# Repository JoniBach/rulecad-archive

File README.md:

# rulecad archive

## Experiments

- **[The robot shoulder printed in place: one print, nothing to assemble but the motor](experiments/print-in-place/)** (2026-11-23): The bench shoulder's compound planetary drawn to come off the bed in one piece: every gap the printer's print gap, herringbone teeth, no carrier, checked by Manifold for gaps and by the slicer's eye for supports. Side by side with the assembled 38:1, with the play each is predicted to have. Predictions only so far: nothing has been printed. [On the site](https://jonibach.github.io/rulecad-archive/experiments/print-in-place/)
- **[What to print to test fixings and frames: five coupons, then a frame](experiments/frames-print-list/)** (2026-11-21): The coupons that turn the fixings and frames estimates into measurements: fixings and holds (pins, magnets, printed bolts), slot, joint rig and printed beam, with what each needs, what it measures and the command that writes it back. [On the site](https://jonibach.github.io/rulecad-archive/experiments/frames-print-list/)
- **[A case of printed beams: a Raspberry Pi 4 case with no bar to buy](experiments/printed-case/)** (2026-11-20): A small case of 2020 beams drawn in aluminium, every beam found printable in PETG, then drawn printed: posts and rails standing up from MISUMI's section, the cross beam lying down from the kit's printable profile, printed brackets, gussets, panels' clips, feet, the board's mount and a fan mount, all on one plate of 73 parts that prints clean. The sag under the board both ways. Predictions only so far: nothing has been printed. [On the site](https://jonibach.github.io/rulecad-archive/experiments/printed-case/)
- **[A frame of beams with a moving axis: cut, drilled, printed and built from one assembly](experiments/frames/)** (2026-11-17): A box of 2020 placed by its ends, with blind joins, printed brackets, feet and a NEMA 17 driving a carriage along its top: the cut list from one bar, a sheet per beam, eight jigs, every printed part on one plate, 37 build steps, and a trapped nut and a plate for the wrong slots caught. Predictions only so far: nothing has been cut or printed. [On the site](https://jonibach.github.io/rulecad-archive/experiments/frames/)
- **[Fixings from rules: a bracket screwed on, and the coupon that measures it](experiments/fixings/)** (2026-11-15): @rulecad/fixings in designs (v.fixings) and fasten in assemblies: each screw followed along its axis for its holes, its far end, its length, its thread, its seat, its key and its load. A shelf bracket with a pilot, an insert boss and nuts in slots, and the fixings coupon to print; measurements to come. [On the site](https://jonibach.github.io/rulecad-archive/experiments/fixings/)
- **[An arm that draws, then lifts, then a leg: checked before it's printed](experiments/robots/)** (2026-11-10): A SCARA arm sized from its task, the same parts upright with a gripper and a Z axis, and a leg from the arm's gearbox, with reach, speed, an error budget, bearing and link loads, wiring, a shopping list and a build page from one assembly. Predictions only so far: nothing has been printed or moved. [On the site](https://jonibach.github.io/rulecad-archive/experiments/robots/)
- **[What to print to test the robots: benchmarks, then the arm, then the leg](experiments/robots-print-list/)** (2026-11-10): The print list and measurements that settle the robot work's three open tests: the bench parts first, then the arm that draws, the same arm lifting, and a leg on a stand, with what each one needs and what it decides. [On the site](https://jonibach.github.io/rulecad-archive/experiments/robots-print-list/)
- **[Benchmarks for a robot joint: every estimate, measured](experiments/benchmarks/)** (2026-11-09): Small parts with plain first layers that measure what a printed robot joint rests on: fits, backlash, a stepper's real torque, what a mesh passes on, and a 38:1 shoulder's play, twist and repeatability. [On the site](https://jonibach.github.io/rulecad-archive/experiments/benchmarks/)
- **[Motors from rules: mounted, driven, and checked before they're bought](experiments/motors/)** (2026-11-09): @rulecad/motors: steppers, gear motors, servos and a brushless motor from their datasheets, with mounts, D-bores and torque curves; motors driving joints in assemblies, checked for torque, speed, holding and heat. A motorised focus slider and a robot shoulder through a 38:1 compound planetary; measurements to come. [On the site](https://jonibach.github.io/rulecad-archive/experiments/motors/)
- **[Gears from rules: spur to bevel, checked before they're printed](experiments/gears/)** (2026-11-08): @rulecad/gears: involute spur gears, racks, rings, helical and herringbone gears, planetaries, worms and bevels from their module and teeth; meshed in phase in assemblies, measured from their drawn teeth, and their teeth analysed by finite elements. A sampler plate to print, a focus slider and a spool winder; measurements to come. [On the site](https://jonibach.github.io/rulecad-archive/experiments/gears/)
- **[Launcher trigger: catching a strong spring and letting it go at once](experiments/launcher-trigger/)** (2026-11-03): Work in progress on the in-line launcher's catch and trigger: a sear whose hinge carries the spring's pull as tension, four layouts tried and what each taught, and the two-stage catch being built next. [On the site](https://jonibach.github.io/rulecad-archive/experiments/launcher-trigger/)
- **[In-line launcher: a cut through the stem's bridge and floor](experiments/launcher-inline-section/)** (2026-11-02): Down the middle of the stem: the bridge prints over it with a 0.6 mm gap, and the stem arches over the floor at 45°. Nothing joins the frame to the pusher.. [On the site](https://jonibach.github.io/rulecad-archive/experiments/launcher-inline-section/)
- **[Mechanisms solved as they would behave: beams that bend, parts that touch, a hand, and a shot](experiments/mechanism-physics/)** (2026-11-02): A large-deflection beam solver, contact, force curves, firing in time and a wave spring, built overnight for printed compliant mechanisms; a key with a tactile click and a wave spring as test pieces, and what it found in the launcher. [On the site](https://jonibach.github.io/rulecad-archive/experiments/mechanism-physics/)
- **[Flat launcher action: a mechanism printed on its side, checked through its whole cycle](experiments/flat-launcher/)** (2026-11-01): The disc launcher's action redrawn as one flat print, the way working printed blasters are made, with new checks for print-in-place gaps, jams, catches that hold and hard stops, and an animation of the cycle. [On the site](https://jonibach.github.io/rulecad-archive/experiments/flat-launcher/)
- **[Disc launcher: a toy pistol whose springs, sear, trigger and feeder are printed flexures](experiments/launcher/)** (2026-10-31): A leaf bow, a snap-hook sear, a trigger on a living hinge and a serpentine feeder, all sized from one rule set; first as one optimised body, then as two cartridges pinned into a frame. [On the site](https://jonibach.github.io/rulecad-archive/experiments/launcher/)
- **[Bin: a lattice wall for the X1C's whole build volume](experiments/bin/)** (2026-10-30): At 5% four legs become pointed arches; at 8% diagonals brace them and the rim is reached: settled, print-ready, 1.06 kg. [On the site](https://jonibach.github.io/rulecad-archive/experiments/bin/)
- **[Flexure samplers: twenty-two flexures and mechanisms to measure](experiments/flexures/)** (2026-10-30): Four printed plates with every flexure in the library and its predicted stiffness and travel; measured, they give the material its strain limit. [On the site](https://jonibach.github.io/rulecad-archive/experiments/flexures/)
- **[Guitar hanger: a wall mount grown from two screws to a cradle](experiments/guitar/)** (2026-10-30): A Telecaster hanger grown from two screw bosses to two arm pads; the second attempt keeps the neck's channel and the screw columns empty, settled in 57 minutes, every check passing. [On the site](https://jonibach.github.io/rulecad-archive/experiments/guitar/)
- **[The force inverter: a mechanism grown from a block](experiments/inverter/)** (2026-10-30): The first generated compliant mechanism; its point hinges, and the robust formulation that gives it real ones. [On the site](https://jonibach.github.io/rulecad-archive/experiments/inverter/)
- **[Tree stand: from stool to goblet to Y to tree](experiments/tree/)** (2026-10-30): Where the loads sit decides whether a part branches; finer cells with bridges gave a lattice canopy, stiffer and print-ready. [On the site](https://jonibach.github.io/rulecad-archive/experiments/tree/)
- **[Bracket bench: four wall brackets of equal mass](experiments/bracket-bench/)** (2026-10-28): Optimised brackets predicted 1.5 times as stiff as a plain web; what printing without supports costs. [On the site](https://jonibach.github.io/rulecad-archive/experiments/bracket-bench/)
- **[L-bracket: stiffest against stress-limited](experiments/lbracket/)** (2026-10-28): Stress limits cut the peak stress by 46% for the same material. [On the site](https://jonibach.github.io/rulecad-archive/experiments/lbracket/)
- **[Lever bench: four levers of equal mass](experiments/lever-bench/)** (2026-10-28): The optimised lever predicted 27 times as stiff as a lightened plate. [On the site](https://jonibach.github.io/rulecad-archive/experiments/lever-bench/)
- **[Twisted tube: the first showcase part](experiments/twist/)** (2026-10-28): Printed in one piece at the second attempt, but with flat blocks and icicles that need supports. [On the site](https://jonibach.github.io/rulecad-archive/experiments/twist/)
- **[Verification: how sure are the predictions?](experiments/verification/)** (2026-10-28): Finer cells showed the first bracket predictions were 15–35% too flexible. [On the site](https://jonibach.github.io/rulecad-archive/experiments/verification/)

## Models

Models made with [rulecad](https://github.com/JoniBach/rulecad), newest first: a picture of each, and a link that opens it in the 3D viewer (turn it, download STL or 3MF). Everything here is public.

- **Add one:** `node add.mjs <workspace> <project>/<object>`, then commit and push.
- **Bring in links shared as Gists:** `node import-gists.mjs`.

### Gripper jaws: opening check

2026-11-23 · `arm/jaws-check` in bench: Compliant gripper jaws from the flexures generator (issue 77) on the arm's yoke: springs grip, the SG90 opens; holds 100 g twice over on 9.4 to 10.5 mm objects. Compare 2026-11-10-arm-gripper-check, the hand-built one

[Open in 3D](https://jonibach.github.io/rulecad-archive/m/2026-11-23-arm-jaws-check/)

### Shoulder printed in place 0.1.0

2026-11-23 · `benchmarks/shoulder-pip` in bench: The bench shoulder's compound planetary printed as one piece on a 17HS4401 (issue 162): 44.3:1, every gap 0.3 mm (0.33 drawn), herringbone teeth, no carrier, the motor on four posts with an M3x8 hex-head screw each. 105 g. Predicted play at the output 3.21 degrees (1.60 mm at the output ring's pitch circle), against 0.65 degrees for the assembled 38:1

[Open in 3D](https://jonibach.github.io/rulecad-archive/m/bench-shoulder-pip/)

### Pot with its lid on

2026-11-23 · `enclosures/snap-pot-closed` in bench: A 60 mm pot whose lid clicks on with an annular snap (fixings annularSnapModel, issue 76): 0.4 mm bead 6 mm under the rim, so the lid's top (5.8 mm over the groove) leaves the skirt free to give; 351 N square push on, 695 N square pull off; hoop strain 0.23% and 0.43%, the skirt's root 0.32%, against PLA's 0.61%; pot 19.3 g, lid 9 g

[Open in 3D](https://jonibach.github.io/rulecad-archive/m/2026-11-23-snap-pot/)

### A leg on a test stand

2026-11-23 · `leg/stand` in bench: On the parts in hand: a 17HS4401 at hip and knee, a 12 V bench supply limited to 1.5 A, DRV8825s at 1/8 step (updated 23 November 2026)

[Open in 3D](https://jonibach.github.io/rulecad-archive/m/2026-11-10-leg-stand/)

### Macropad, module behind the top row: Choc keys

2026-11-22 · `thin-picro/macropad-rear` in thin-picro: Built: 12 Choc v1 switches with low-profile caps on a through-hole 4 x 3 matrix, the thin module under the top row on pin headers, parts down; 59.7 x 76.9 mm board, 18.3 mm tall, every check passing, no parts overlapping. Not built yet

[Open in 3D](https://jonibach.github.io/rulecad-archive/m/thin-module-macropad-rear/)

### Macropad, module on top: MX keys and a 2.0 in display

2026-11-22 · `thin-picro/macropad-front` in thin-picro: Built: 12 MX switches with DSA caps on a through-hole 4 x 3 matrix (a DO-35 per key), the thin module soldered flat at the board's top edge, a 2.0 in ST7789 plugged straight into the module and lying over it, clear of the keys. 65.2 x 106.5 mm board, every check passing. Not built yet

[Open in 3D](https://jonibach.github.io/rulecad-archive/m/thin-module-macropad-front/)

### The arm upright: it lifts

2026-11-22 · `arm/arm-upright` in bench: The same arm upright with the gripper, on the parts in hand: 17HS4401s, 12 V, the pen lift's SG90 moved to the gripper (updated 22 November 2026)

[Open in 3D](https://jonibach.github.io/rulecad-archive/m/2026-11-10-arm-arm-upright/)

### SCARA arm that draws

2026-11-22 · `arm/arm` in bench: On the parts in hand: a 17HS4401 at both joints, a 12 V bench supply, DRV8825s at 1/8 step, one SG90 (updated 22 November 2026)

[Open in 3D](https://jonibach.github.io/rulecad-archive/m/2026-11-09-arm-arm/)

### Holds coupon 0.1.0

2026-11-21 · `benchmarks/holds-coupon` in bench: Printed with the fixings coupon on one plate: printed M8 and M10 bolts and nuts, a pull bolt, snap pins, dowel and filament pin holes, magnet pockets (MEASURE.md rows 40 to 47)

[Open in 3D](https://jonibach.github.io/rulecad-archive/m/bench-holds-coupon/)

### Beam coupon

2026-11-21 · `benchmarks/beam-test` in bench: Print 10: a printed 1515 beam lying down (k1) and one standing up (k2), 240 mm, on two bars 220 mm apart, for its sag and break (rows 38, 39); once in each plastic

[Open in 3D](https://jonibach.github.io/rulecad-archive/m/bench-beam-coupon/)

### Joint rig

2026-11-21 · `benchmarks/joint-test` in bench: Print 9: three hangers, the dial arm, the nut puller and a printed corner bracket on a 2020 base beam, for a blind join, a printed bracket, a bought fitting and a slot nut (rows 34 to 37)

[Open in 3D](https://jonibach.github.io/rulecad-archive/m/bench-joint-rig/)

### Slot coupon 0.1.0

2026-11-21 · `benchmarks/slot-coupon` in bench: Print 8: tongues, carriers and printed slots for slot 6 and slot 8 beams, 26 loose pieces (rows 29 to 33)

[Open in 3D](https://jonibach.github.io/rulecad-archive/m/bench-slot-coupon/)

### Fixings coupon 0.1.0

2026-11-21 · `benchmarks/fixings-coupon` in bench: Print 7 on MEASURE.md: pilots, inserts, nut pockets and slots, counterbore, printed threads and flank forms (rows 22 to 28); once in PLA, once in PETG

[Open in 3D](https://jonibach.github.io/rulecad-archive/m/fixings-coupon/)

### The case, every beam printed: base, plate 1

2026-11-20 · `case/printed-base-1` in ws17: The printed case's one plate: 73 PETG parts, 593 g, laid as each prints

[Open in 3D](https://jonibach.github.io/rulecad-archive/m/2026-11-20-printed-case-plate/)

### The case, every beam printed

2026-11-20 · `case/printed` in ws17: A Raspberry Pi 4 case with every beam printed in PETG: EXAMPLES chapter 17

[Open in 3D](https://jonibach.github.io/rulecad-archive/m/2026-11-20-printed-case/)

### Thin RP2040 module 0.7.2

2026-11-20 · `thin-picro/module` in thin-picro: 0.7.2: tracks finished for the fab (square pad exits, acute corners filled) after an engineer's review; fab files plotted and checked by KiCad, the JLCPCB zip in the link. Not yet built

[Open in 3D](https://jonibach.github.io/rulecad-archive/m/thin-rp2040-module/)

### A box of 2020 with a moving axis

2026-11-17 · `frame/box` in ws16: A box of 2020 placed by its ends: blind joins, printed brackets, feet and caps, a NEMA 17 driving a carriage on two rods along the top front rail (99.5 mm of travel); drag the carriage's slider to sweep it along its axis

[Open in 3D](https://jonibach.github.io/rulecad-archive/m/2026-11-17-frame-box/)

### A shelf bracket on its wall plate

2026-11-15 · `fix/shelf` in examples: EXAMPLES chapter 15: a shelf bracket on its wall plate, a pilot, an insert boss and two nuts in slots, each screw checked by fasten

[Open in 3D](https://jonibach.github.io/rulecad-archive/m/fixings-shelf-bracket/)

### XIAO core, 32 mm

2026-11-13 · `xiaocore/core` in hardware: A 32 mm core for a XIAO ESP32-C6: a four-layer carrier board with spring contacts on every side and spring pins to a wall seat underneath, in a shell with a two-clip lid. Poses show the lid and board going in.

[Open in 3D](https://jonibach.github.io/rulecad-archive/m/xiao-core-32/)

### Motorised spool winder

2026-11-13 · `home/winder-driven` in ws3: The spool winder with an N20 on the sun: the spool on the carrier, 4:1, 2.25 times the torque a 10 N strap needs on a 150:1 N20; draft PR 208

[Open in 3D](https://jonibach.github.io/rulecad-archive/m/2026-11-13-winder-driven/)

### Gripper: closing check

2026-11-13 · `arm/gripper-check` in bench

[Open in 3D](https://jonibach.github.io/rulecad-archive/m/2026-11-10-arm-gripper-check/)

### Shoulder input lever 0.1.0

2026-11-13 · `benchmarks/input-lever` in bench: A printed copy of the motor's shaft on a lever, to turn the shoulder's sun by hand.

[Open in 3D](https://jonibach.github.io/rulecad-archive/m/bench-input-lever/)

### 17HS4401 on the test stand

2026-11-13 · `benchmarks/motor-test` in bench: A 17HS4401 on a stand, with a dial and a 100 mm arm: holding, detent, speed and heat.

[Open in 3D](https://jonibach.github.io/rulecad-archive/m/bench-motor-stand/)

### Robot shoulder on the test stand

2026-11-13 · `benchmarks/shoulder-test` in bench: The 38:1 compound planetary on the stand: solid base, dial and pointer.

[Open in 3D](https://jonibach.github.io/rulecad-archive/m/bench-shoulder/)

### Thin RP2040 module (with-headers) 0.7.1

2026-11-11 · `thin-picro/module:with-headers` in thin-picro: The thin module fitted with 2.54 mm pin headers (3D only; the board is the same)

[Open in 3D](https://jonibach.github.io/rulecad-archive/m/thin-rp2040-module-headers/)

### Seats coupon 0.1.0

2026-11-10 · `benchmarks/seats-coupon` in bench

[Open in 3D](https://jonibach.github.io/rulecad-archive/m/bench-seats-coupon/)

### Mesh rig on the stand

2026-11-09 · `benchmarks/mesh-rig-test` in bench: One spur pair with a lever each, for what a printed mesh passes on.

[Open in 3D](https://jonibach.github.io/rulecad-archive/m/bench-mesh-rig/)

### SG90 on its stand

2026-11-09 · `benchmarks/servo-test` in bench: An SG90 in a solid block, with a 60 mm arm.

[Open in 3D](https://jonibach.github.io/rulecad-archive/m/bench-servo-stand/)

### Gear card, mounted

2026-11-09 · `benchmarks/card-mounted` in bench: Nine gear pairs on one solid card: three modules, three backlashes. Measures 1 and 2.

[Open in 3D](https://jonibach.github.io/rulecad-archive/m/bench-gear-card/)

### Fit bar 0.1.0

2026-11-09 · `benchmarks/fit-bar` in bench: Stepped holes, D-bores and M3 pilots in one solid block: measures 3, 4 and 5.

[Open in 3D](https://jonibach.github.io/rulecad-archive/m/bench-fit-bar/)

### Robot shoulder

2026-11-09 · `home/shoulder` in ws: A NEMA 17 through a 38:1 compound planetary: 7.4 N m at the output, 500 g at 150 mm with ten times to spare, holds unpowered.

[Open in 3D](https://jonibach.github.io/rulecad-archive/m/motors-robot-shoulder/)

### Motorised focus slider

2026-11-09 · `home/driven` in ws: A focus slider on a 28BYJ-48 stepper: 4.7 N at the slide against the 1 N it pushes, 6.4 mm/s, holds with the power off.

[Open in 3D](https://jonibach.github.io/rulecad-archive/m/motors-focus-slider/)

### Strap tensioner

2026-11-08 · `gears/tensioner` in bench: A crank through two herringbone stages (6 : 1, module 1.25) to a spool held by a ratchet, on a skeleton frame with printed pins; the pawl on two push pins; the crank arm seated over the shaft's flat. Sized for a 100 N strap at about 2×: 4.6 N at the crank. 86 g of PLA

[Open in 3D](https://jonibach.github.io/rulecad-archive/m/gears-strap-tensioner/)

### Spool winder

2026-11-08 · `home/winder` in worked-examples: A planetary gearbox, 4 : 1: the crank on the carrier, the spool on the sun, teeth from planetary() (18/18/54), every planet in phase; the ring held to the spoked case by two push pins. 28 g of PLA. Worked example 9; not printed yet

[Open in 3D](https://jonibach.github.io/rulecad-archive/m/gears-spool-winder/)

### Focus slider

2026-11-08 · `home/slider` in worked-examples: A rack and pinion: a 14-tooth pinion with a knob on an axle printed with the base, the rack sliding against a guide, 43.98 mm a turn. 13 g of PLA. Worked example 8; not printed yet

[Open in 3D](https://jonibach.github.io/rulecad-archive/m/gears-focus-slider/)

### Gear sampler, mounted

2026-11-08 · `gears/sampler-mounted` in bench: The gear sampler put together: nine pairs (modules 0.8, 1, 1.5 by backlash 0.1, 0.2, 0.3 mm) on a ladder frame, each pair meshed at the play it was drawn with, a rack on its rail and a ring in its lip. 59 g of PLA. Not printed yet

[Open in 3D](https://jonibach.github.io/rulecad-archive/m/gears-sampler-mounted/)

### Launcher action, in line: a pusher between two curved arms shaped by the beam solver, a flooded frame, the disc flat in a roofed slot, the pull ring on top, a solid trigger that is its own sear on a hinge carrying the pull, printed in one piece on its side (catch) 0.9.3

2026-11-07 · `launcher/inline:catch` in bench: 0.9.3: the catch and trigger alone, as in the launcher (no straps on this piece; the version follows the launcher's)

[Open in 3D](https://jonibach.github.io/rulecad-archive/m/launcher-inline-catch/) · [Play its sequence](https://jonibach.github.io/rulecad-archive/m/launcher-inline-catch/play.html)

### Launcher action, in line: a pusher between two curved arms shaped by the beam solver, a flooded frame, the disc flat in a roofed slot, the pull ring on top, a solid trigger that is its own sear on a hinge carrying the pull, printed in one piece on its side 0.9.3

2026-11-07 · `launcher/inline` in bench: 0.9.3: the strap pockets' ceilings slant in at 45° beside the slots, so no ledge prints flat in the air over a strap

[Open in 3D](https://jonibach.github.io/rulecad-archive/m/launcher-inline/) · [Play its sequence](https://jonibach.github.io/rulecad-archive/m/launcher-inline/play.html)

### Launcher action, in line: a pusher between two curved arms shaped by the beam solver, a flooded frame, the disc flat in a roofed slot, the stem trapped in a guide, a hooked sear on one flexure and a trigger blade, printed in one piece on its side 0.8.0

2026-11-03 · `launcher/inline` in bench: Work in progress (branch trigger-wip): catch over the stem ahead of the ring, trigger block and shaped hinge in the frame's room above the ring. Cocks, holds and lets go in the simulation; pull heavy (6.5 N), not yet printable.

[Open in 3D](https://jonibach.github.io/rulecad-archive/m/launcher-inline-wip/) · [Play its sequence](https://jonibach.github.io/rulecad-archive/m/launcher-inline-wip/play.html)

### Modular station concept, 48 mm: print plate

2026-11-02 · `concept48/print` in hardware: Every part on one bed, each its own object, ready to print

[Open in 3D](https://jonibach.github.io/rulecad-archive/m/station-concept-48-print/)

### Modular station concept, 48 mm

2026-11-02 · `concept48/station` in hardware: Rough casing concept: core, pods and a compact pack

[Open in 3D](https://jonibach.github.io/rulecad-archive/m/station-concept-48/)

### A wave spring: a plunger on legs joined by round bends, squashed in a channel until it stacks solid 0.1.0

2026-11-02 · `mechanisms/wave` in bench

[Open in 3D](https://jonibach.github.io/rulecad-archive/m/mechanisms-wave/)

### A printed key with a tactile click: a stem on a two-leaf guide, a bump riding past a bump on a leaf 0.1.0

2026-11-02 · `mechanisms/key` in bench

[Open in 3D](https://jonibach.github.io/rulecad-archive/m/mechanisms-key/) · [Play its sequence](https://jonibach.github.io/rulecad-archive/m/mechanisms-key/play.html)

### Launcher action, flat: a pusher on a tapered two-leaf spring, a trigger that is its own sear, printed in one piece on its side 0.1.0

2026-11-02 · `launcher/flat` in bench

[Open in 3D](https://jonibach.github.io/rulecad-archive/m/launcher-flat/)

### Launcher fit test: chamber, sled, free-standing leaves and pins at three clearances each 0.1.0

2026-10-31 · `launcher/fittest` in bench: Fit test before the launcher's redesign: disc and sled channels, free-standing leaves and pins, three clearances each, labelled

[Open in 3D](https://jonibach.github.io/rulecad-archive/m/launcher-fittest/)

### The disc launcher: the frame with its two cartridges pinned in, the sled, the magazine insert and a disc, at rest

2026-10-31 · `launcher/launcher` in bench: The launcher at rest, about 127 × 112 × 26 mm: the frame, two cartridges pinned in, the sled, the magazine insert and a disc; every fit checked

[Open in 3D](https://jonibach.github.io/rulecad-archive/m/launcher-2/)

### The disc: what the launcher throws 0.1.0

2026-10-31 · `launcher/disc` in bench: The disc: 20 × 2 mm, chamfered, a dimple on top

[Open in 3D](https://jonibach.github.io/rulecad-archive/m/launcher-disc/)

### The sled: pushed by the bow, it pushes the disc 0.1.0

2026-10-31 · `launcher/sled` in bench: The sled: plate and nose under the magazine, a rod back to the tab the bow pushes, and the cocking ring

[Open in 3D](https://jonibach.github.io/rulecad-archive/m/launcher-sled/)

### The magazine insert: follower, serpentine spring and a snap-in cap in one piece 0.1.0

2026-10-31 · `launcher/magazine` in bench: The magazine insert as printed: follower, open serpentine and a snap-in cap

[Open in 3D](https://jonibach.github.io/rulecad-archive/m/launcher-magazine/)

### The barrel cartridge: the slot the sled and the disc run in, with the magazine column over its mouth 0.1.0

2026-10-31 · `launcher/barrel` in bench: The barrel cartridge: the slot out through the muzzle, the magazine column, the hollow for the pins

[Open in 3D](https://jonibach.github.io/rulecad-archive/m/launcher-barrel/)

### The action cartridge: bow, sear and trigger printed in place in a tray that pins into the frame 0.1.0

2026-10-31 · `launcher/action` in bench: The action cartridge as printed: the bow straight, the sear and the trigger; the assembly's cocked pose bends the bow

[Open in 3D](https://jonibach.github.io/rulecad-archive/m/launcher-action/)

### The frame: grip with a palm swell, receiver and trigger guard round two cavities the cartridges pin into 0.1.0

2026-10-31 · `launcher/frame` in bench: The frame, scaled down: 110 × 107 × 26 mm, a rounded skin round two cavities, a palm swell, the trigger guard, the muzzle, six teardrop pin holes

[Open in 3D](https://jonibach.github.io/rulecad-archive/m/launcher-frame/)

### The body: bow, sear and trigger printed in place, the magazine column and the barrel, on an optimised frame 0.1.0

2026-10-31 · `launcher/body` in bench: The body on its optimised frame: bow, sear and trigger printed in place, the magazine column, the barrel; 164 g, every check passing

[Open in 3D](https://jonibach.github.io/rulecad-archive/m/launcher-body/)

### Guitar hanger: optimised 0.1.0

2026-10-31 · `showcase/guitar` in bench: Second attempt: the neck's channel and a driver column over each screw kept empty; drawn at print resolution and sliced clean: no islands in 350 layers

[Open in 3D](https://jonibach.github.io/rulecad-archive/m/guitar-2/)

### Flexure sampler 4: travel stops, a curved leaf, a contact-aided leaf, a parallelogram and tweezers 0.1.0

2026-10-30 · `flexures/sampler4` in bench: Stops and mechanisms made compliant: a leaf with travel stops where the strain limit says, a pre-curved leaf, a contact-aided leaf with two rates, a parallelogram four-bar on notch hinges, and tweezers on a post

[Open in 3D](https://jonibach.github.io/rulecad-archive/m/flexure-sampler-4/)

### Flexure sampler 3: a folded guide, a cartwheel pivot, an elliptical hinge, two snap hooks and a ratchet 0.1.0

2026-10-30 · `flexures/sampler3` in bench: Things that click, turn and hold: a folded-beam guide, a cartwheel pivot, an elliptical notch hinge, two snap hooks under catch lips (gaps widened to the fit plus a margin after the first print fused them), and a ratchet wheel to pin on a boss beside its pawl

[Open in 3D](https://jonibach.github.io/rulecad-archive/m/flexure-sampler-3/)

### Guitar hanger: optimised 0.1.0

2026-10-30 · `showcase/guitar` in bench: A wall hanger that cradles a Telecaster's neck: grown from two screw bosses to the two pads the headstock rests on, against the guitar's weight, a tug and a knock; settled at step 234, printable lying on its back

[Open in 3D](https://jonibach.github.io/rulecad-archive/m/guitar/)

### Joints that aren't flexures: a pin joint printed in place, and a snap pin with its socket 0.1.0

2026-10-30 · `flexures/joints` in bench: Joints that aren't flexures, for comparison: a pin joint printed in place that breaks free with a twist, and a snap pin standing beside its socket

[Open in 3D](https://jonibach.github.io/rulecad-archive/m/flexure-joints/)

### Flexure sampler 2: a compound guide, a constant-force mechanism and a LET joint, on one rail 0.1.0

2026-10-30 · `flexures/sampler2` in bench: Three mechanisms on one rail: a compound parallel guide (no drop), a constant-force slider-crank with a leaf coupler and filament pins, and a LET joint cut into a six-layer sheet

[Open in 3D](https://jonibach.github.io/rulecad-archive/m/flexure-sampler-2/)

### Bin: optimised lattice wall 0.1.0

2026-10-30 · `showcase/bin` in bench: Third attempt, 8% of the space: a lattice wall settled at step 211, one piece, printable without supports

[Open in 3D](https://jonibach.github.io/rulecad-archive/m/bin-3/)

### Tree stand: optimised 0.1.0

2026-10-30 · `showcase/tree` in bench: Sixth attempt, 1.5 mm cells with the bridged overhang filter: converged at step 347, one piece, printable without supports

[Open in 3D](https://jonibach.github.io/rulecad-archive/m/tree-6/)

### Flexure sampler: seven flexures at three thicknesses, on two rails 0.1.0

2026-10-30 · `flexures/sampler` in bench: The flexure sampler: seven kinds of flexure at two, three and four lines thick on two rails, 152 × 122 × 8 mm, printed flat so every one bends within its layers. Each has a predicted stiffness and travel to 2% strain to measure against.

[Open in 3D](https://jonibach.github.io/rulecad-archive/m/flexure-sampler/)

### A leaf spring on its block, at rest and pressed (pressed) 0.1.0

2026-10-30 · `flexures/spring:pressed` in bench: A leaf spring (40 × 1.26 × 8 mm, PLA) on its block, drawn pressed 15 mm sideways by the elastica: the tip has come 2.5 mm nearer the block and turned. From the flexure bench (@rulecad/flexures).

[Open in 3D](https://jonibach.github.io/rulecad-archive/m/spring-pressed/)

### Bin: optimised lattice wall 0.1.0

2026-10-29 · `showcase/bin` in bench: Second attempt, at 5% of the cylinder (about 17% of the wall): four legs rise from the foot ring into pointed arches that meet under the rim, like a crown. One piece, nothing in mid-air, no overhang past 45° (the design's ledge under the rim slopes a touch steeper than 45°). 664 g of PLA; leant on 4,240 N/mm, kicked 54 N/mm; 300 steps in an hour on the faster solver, not settled, and 17% of the kept rim had nothing under it before the ledge. On 6 mm cells the optimiser can't bridge (its reach rounds to zero).

[Open in 3D](https://jonibach.github.io/rulecad-archive/m/bin-2/)

### Tree stand: optimised 0.1.0

2026-10-29 · `showcase/tree` in bench: Fifth attempt, complete and print-ready: a trunk from all three feet, branching into a canopy under the plate. With a sideways push from three directions every foot is needed. One piece, nothing in mid-air, no overhang past 45°, bridges 2.6 mm; 32 g of PLA, 4,380 N/mm down, 126–133 N/mm sideways; 300 steps in 50 min on the faster solver.

[Open in 3D](https://jonibach.github.io/rulecad-archive/m/tree-5/)

### Tree stand: optimised 0.1.0

2026-10-29 · `showcase/tree` in bench: Fourth attempt, on the faster solver with kept regions held up: the trunk splits into branches that fan out under the plate, and every bridge is short (2.6 mm), nothing starts in mid-air, no overhang past 45°. But the trunk grows from two feet and the third, kept, sits loose: the loads never needed it. 10% of the space, 3,960 N/mm down; 300 steps, not settled, 22 min.

[Open in 3D](https://jonibach.github.io/rulecad-archive/m/tree-4/)

### Bin: optimised lattice wall 0.1.0

2026-10-29 · `showcase/bin` in bench: First attempt, too heavy and not yet support-free: 230 × 250 mm, a wall that's mostly solid with tall pointed-arch windows (the 45° rule's own shape), about 2 kg of PLA. The 15% share counted the whole cylinder, the empty inside too, so it filled half the wall; about 4–5% would give a lattice. Leant on: 35,700 N/mm; kicked: 1,380 N/mm. The print check still finds 523 mm² past 45° and two tips under the rim. 246 steps on 76,800 cells of 6 mm in about 4 hours.

[Open in 3D](https://jonibach.github.io/rulecad-archive/m/bin/)

### Tree stand: optimised 0.1.0

2026-10-29 · `showcase/tree` in bench: Third attempt: a Y. A trunk rises from the feet and splits into three arms under the plate, one to each load. 10% of the space, three loads between the feet, no twist. In one piece apart from four specks of 1–2 cells, no overhangs past 45°, bridges 3.3 mm; 32 g of PLA; 239 steps in 87 min.

[Open in 3D](https://jonibach.github.io/rulecad-archive/m/tree-3/)

### Tree stand: optimised 0.1.0

2026-10-29 · `showcase/tree` in bench: Second attempt: a goblet, not a tree. With the feet together as a trunk and the load round the plate's edge, it grew a cone flaring out at 45° to the plate. The twisting case and six evenly spaced loads favour a closed shell over separate branches. In one piece, no overhangs past 45°, bridges 2.6 mm; 48 g of PLA; 266 steps in 55 min.

[Open in 3D](https://jonibach.github.io/rulecad-archive/m/tree-2/)

### Tree stand: optimised 0.1.0

2026-10-29 · `showcase/tree` in bench: First attempt: came out as a stool, three straight legs under a plate, not a tree. The loads sit right above the feet and the solid plate spreads them, so straight columns are stiffest. In one piece, prints standing on its feet with 3 mm bridges under the plate, 48 g of PLA; 237 steps on 40,960 cells in 49 min.

[Open in 3D](https://jonibach.github.io/rulecad-archive/m/tree/)

### Twisted tube: optimised 0.1.0

2026-10-28 · `showcase/twist` in bench: Second attempt, in one piece: 25% of a 40 × 80 mm cylinder with struts at least 5 mm thick. The wall opens into diamond windows running round it in a spiral. 249 steps on 23,040 cells of 2 mm in 19 min; printable standing up, 32 g of PLA.

[Open in 3D](https://jonibach.github.io/rulecad-archive/m/twist-2/)

### Twisted tube, first attempt: falls apart

2026-10-28 · `showcase/twist` in bench: Failed: the struts came out one cell thick, and a one-cell strut at 45° on a cube grid touches only at edges, so the part fell into 11 pieces with many thin, non-solid bits. Settings: 15% of a 40 × 80 mm cylinder, filter 3 mm on 2 mm cells. Rerun with a 5 mm filter and 25% material.

[Open in 3D](https://jonibach.github.io/rulecad-archive/m/twist/)

### Lever bench: optimised lever (both) 0.1.0

2026-10-28 · `bench/lever:both` in bench: optimised for two loads

[Open in 3D](https://jonibach.github.io/rulecad-archive/m/lever-d/)

### Lever bench: lightened plate 0.1.0

2026-10-28 · `bench/lever-plate` in bench: a plate with four windows

[Open in 3D](https://jonibach.github.io/rulecad-archive/m/lever-b/)

### Lever bench: plain bar 0.1.0

2026-10-28 · `bench/lever-bar` in bench: a plain bar

[Open in 3D](https://jonibach.github.io/rulecad-archive/m/lever-a/)

### Bracket bench: optimised bracket (side-free) 0.1.0

2026-10-28 · `bench/bracket:side-free` in bench: B laid on its side: what it would need supporting

[Open in 3D](https://jonibach.github.io/rulecad-archive/m/bracket-b-side/)

### Bracket bench: optimised bracket 0.1.0

2026-10-28 · `bench/bracket` in bench: optimised freely

[Open in 3D](https://jonibach.github.io/rulecad-archive/m/bracket-b/)

### Bracket bench: plain web 0.1.0

2026-10-28 · `bench/bracket-web` in bench: the plain web: the hand-made bracket

[Open in 3D](https://jonibach.github.io/rulecad-archive/m/bracket-a/)

### L-bracket: lightest under 25 MPa

2026-10-28 · `lbracket/stress` in rulecad topopt reference: the lightest under 25 MPa; peak 36.6 MPa as made

[Open in 3D](https://jonibach.github.io/rulecad-archive/m/lbracket-stress/)

### L-bracket: stiffest at 40%

2026-10-28 · `lbracket/stiffest` in rulecad topopt reference: the stiffest at 40% of the space; peak 67.2 MPa as made

[Open in 3D](https://jonibach.github.io/rulecad-archive/m/lbracket-stiffest/)

### Bracket bench: optimised bracket

2026-10-28 · `bench/bracket` in rulecad examples: as shared

[Open in 3D](https://jonibach.github.io/rulecad-archive/m/bench-bracket/)

### Bracket bench: plain web

2026-10-28 · `bench/bracket-web` in rulecad examples: as shared

[Open in 3D](https://jonibach.github.io/rulecad-archive/m/bench-bracket-web/)

### Bracket bench, assembled

2026-10-28 · `bench/bracket-bench` in rulecad examples: as shared

[Open in 3D](https://jonibach.github.io/rulecad-archive/m/bench-bracket-bench/)

### Lever bench: optimised lever 0.1.0

2026-10-28 · `bench/lever` in bench: the stiffest lever for its load, 2D

[Open in 3D](https://jonibach.github.io/rulecad-archive/m/lever-c/)

### Bracket bench: optimised bracket (side) 0.1.0

2026-10-28 · `bench/bracket:side` in bench: optimised to print without supports, lying on its side

[Open in 3D](https://jonibach.github.io/rulecad-archive/m/bracket-d/)

### Bracket bench: optimised bracket (printable) 0.1.0

2026-10-28 · `bench/bracket:printable` in bench: optimised to print without supports, standing on its back plate

[Open in 3D](https://jonibach.github.io/rulecad-archive/m/bracket-c/)

### Legion Go folio (Cherry MX)

2026-10-27 · `legion-go-mx/folio` in mirror-cad: as shared

[Open in 3D](https://jonibach.github.io/rulecad-archive/m/legion-go-mx-folio/)

### Legion Go folio: 57 keycaps

2026-10-27 · `legion-go-mx/keycaps` in mirror-cad: as shared

[Open in 3D](https://jonibach.github.io/rulecad-archive/m/legion-go-mx-keycaps/)

### Lever bench: optimised lever

2026-10-27 · `lever/optimised` in rulecad examples: as shared

[Open in 3D](https://jonibach.github.io/rulecad-archive/m/lever-optimised/)

### Lever bench: optimised lever (both)

2026-10-27 · `lever/optimised:both` in rulecad examples: as shared

[Open in 3D](https://jonibach.github.io/rulecad-archive/m/lever-optimised-both/)

### Lever bench, assembled

2026-10-27 · `lever/bench` in rulecad examples: as shared

[Open in 3D](https://jonibach.github.io/rulecad-archive/m/lever-bench/)

### Legion Go folio

2026-10-26 · `legion-go/folio` in mirror-cad: as shared

[Open in 3D](https://jonibach.github.io/rulecad-archive/m/legion-go-folio/)

### Legion Go rail test piece

2026-10-25 · `legion-go/rail-test` in mirror-cad: as shared

[Open in 3D](https://jonibach.github.io/rulecad-archive/m/legion-go-rail-test/)

### Legion Go rail test (full)

2026-10-25 · `legion-go/rail-test:full` in mirror-cad: as shared

[Open in 3D](https://jonibach.github.io/rulecad-archive/m/legion-go-rail-test-full/)

### Legion Go rail test (short)

2026-10-25 · `legion-go/rail-test:short` in mirror-cad: as shared

[Open in 3D](https://jonibach.github.io/rulecad-archive/m/legion-go-rail-test-short/)

### Legion Go hinge foot

2026-10-25 · `legion-go/hinge-foot` in mirror-cad: as shared

[Open in 3D](https://jonibach.github.io/rulecad-archive/m/legion-go-hinge-foot/)

### Legion Go keyboard case

2026-10-25 · `legion-go/keyboard` in mirror-cad: as shared

[Open in 3D](https://jonibach.github.io/rulecad-archive/m/legion-go-keyboard/)

### Legion Go rail test (box-short)

2026-10-25 · `legion-go/rail-test:box-short` in mirror-cad: as shared

[Open in 3D](https://jonibach.github.io/rulecad-archive/m/legion-go-rail-test-box-short/)

### Legion Go folio: folded shut

2026-10-25 · `legion-go/folded` in mirror-cad: as shared

[Open in 3D](https://jonibach.github.io/rulecad-archive/m/legion-go-folded/)

### Legion Go folio: open flat

2026-10-25 · `legion-go/flat` in mirror-cad: as shared

[Open in 3D](https://jonibach.github.io/rulecad-archive/m/legion-go-flat/)

### Legion Go folio: tablet mode

2026-10-25 · `legion-go/tablet` in mirror-cad: as shared

[Open in 3D](https://jonibach.github.io/rulecad-archive/m/legion-go-tablet/)

### Legion Go side mount

2026-10-25 · `legion-go/mount` in mirror-cad: as shared

[Open in 3D](https://jonibach.github.io/rulecad-archive/m/legion-go-mount/)

### Legion Go folio: open

2026-10-25 · `legion-go/stand` in mirror-cad: as shared

[Open in 3D](https://jonibach.github.io/rulecad-archive/m/legion-go-stand/)

### Legion Go folio: open

2026-10-25 · `legion-go-mx/stand` in mirror-cad: as shared

[Open in 3D](https://jonibach.github.io/rulecad-archive/m/legion-go-mx-stand/)

### Legion Go folio: folded shut

2026-10-25 · `legion-go-mx/folded` in mirror-cad: as shared

[Open in 3D](https://jonibach.github.io/rulecad-archive/m/legion-go-mx-folded/)

### Legion Go folio: open flat

2026-10-25 · `legion-go-mx/flat` in mirror-cad: as shared

[Open in 3D](https://jonibach.github.io/rulecad-archive/m/legion-go-mx-flat/)

### Legion Go folio: tablet mode

2026-10-25 · `legion-go-mx/tablet` in mirror-cad: as shared

[Open in 3D](https://jonibach.github.io/rulecad-archive/m/legion-go-mx-tablet/)

### Staggered keyboard: 55 keycaps

2026-10-14 · `keyboard/staggered-keycaps` in mirror-cad: as shared

[Open in 3D](https://jonibach.github.io/rulecad-archive/m/keyboard-staggered-keycaps/)

### 9-key macropad PCB

2026-10-14 · `keyboard/macropad-pcb` in mirror-cad: as shared

[Open in 3D](https://jonibach.github.io/rulecad-archive/m/keyboard-macropad-pcb/)

### Staggered keyboard PCB

2026-10-14 · `keyboard/main-pcb` in mirror-cad: as shared

[Open in 3D](https://jonibach.github.io/rulecad-archive/m/keyboard-main-pcb/)

### Staggered PCB keyboard

2026-10-14 · `keyboard/staggered-pcb` in mirror-cad: as shared

[Open in 3D](https://jonibach.github.io/rulecad-archive/m/keyboard-staggered-pcb/)

### MX keycap

2026-10-14 · `keyboard/keycap` in mirror-cad: as shared

[Open in 3D](https://jonibach.github.io/rulecad-archive/m/keyboard-keycap/)

### 9-key macropad

2026-10-14 · `keyboard/macropad-3x3` in mirror-cad: as shared

[Open in 3D](https://jonibach.github.io/rulecad-archive/m/keyboard-macropad-3x3/)

### Staggered keyboard: plate

2026-10-13 · `keyboard/staggered-plate` in mirror-cad: as shared

[Open in 3D](https://jonibach.github.io/rulecad-archive/m/keyboard-staggered-plate/)

### MX keycap (legend-f)

2026-10-13 · `keyboard/keycap:legend-f` in mirror-cad: as shared

[Open in 3D](https://jonibach.github.io/rulecad-archive/m/keyboard-keycap-legend-f/)

### MX keycap (legend-shift)

2026-10-13 · `keyboard/keycap:legend-shift` in mirror-cad: as shared

[Open in 3D](https://jonibach.github.io/rulecad-archive/m/keyboard-keycap-legend-shift/)

### Staggered keyboard: case

2026-10-13 · `keyboard/staggered-case` in mirror-cad: as shared

[Open in 3D](https://jonibach.github.io/rulecad-archive/m/keyboard-staggered-case/)

### Staggered handwired keyboard

2026-10-13 · `keyboard/staggered` in mirror-cad: as shared

[Open in 3D](https://jonibach.github.io/rulecad-archive/m/keyboard-staggered/)

### Handwired 40% keyboard

2026-10-12 · `keyboard/handwired-40` in mirror-cad: as shared

[Open in 3D](https://jonibach.github.io/rulecad-archive/m/keyboard-handwired-40/)

### Handwired 40%: case

2026-10-12 · `keyboard/handwired-40-case` in mirror-cad: as shared

[Open in 3D](https://jonibach.github.io/rulecad-archive/m/keyboard-handwired-40-case/)

### Handwired 40%: plate

2026-10-12 · `keyboard/handwired-40-plate` in mirror-cad: as shared

[Open in 3D](https://jonibach.github.io/rulecad-archive/m/keyboard-handwired-40-plate/)

### Handwired 40%: 48 keycaps

2026-10-12 · `keyboard/handwired-40-keycaps` in mirror-cad: as shared

[Open in 3D](https://jonibach.github.io/rulecad-archive/m/keyboard-handwired-40-keycaps/)

### 9-key macropad, print plate

2026-10-11 · `keyboard/macropad-3x3-print` in mirror-cad: as shared

[Open in 3D](https://jonibach.github.io/rulecad-archive/m/keyboard-macropad-3x3-print/)

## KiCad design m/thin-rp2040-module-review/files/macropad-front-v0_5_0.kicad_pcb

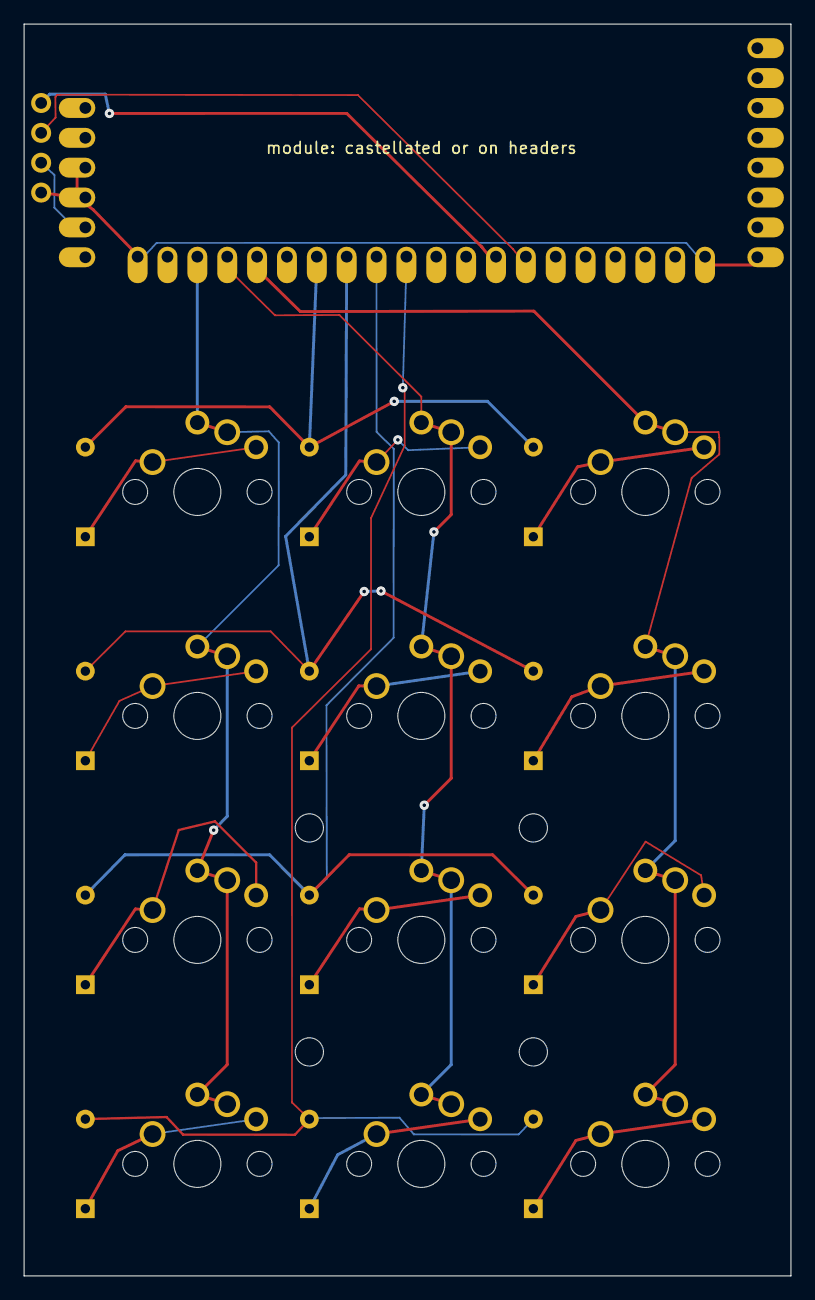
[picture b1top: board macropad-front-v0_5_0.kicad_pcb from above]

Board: 2 copper layers, 65.2 x 106.5 mm, 26 parts (0 on the bottom side), 23 nets.

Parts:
D1, D2, D3, D4, D5, D6, D7, D8, D9, D10, D11, D12: D; 1N4148
J2: 1 × 4 female header, 2.54 mm; 1_4_female_header_2_54_mm
K1, K2, K3, K4, K5, K6, K7, K8, K9, K10, K11, K12: Cherry MX or Kailh Choc v1 (PCB mount); Cherry_MX_or_Kailh_Choc_v1_PCB_mount
U1: thin RP2040 module; thin_RP2040_module

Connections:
3V3: J2.2, U1.35
COL0: K1.1, K4.1, K7.1, K10.1, U1.21
COL1: K2.1, K5.1, K8.1, K11.1, U1.19
COL2: K3.1, K6.1, K9.1, K12.1, U1.22
GND: J2.1, U1.4, U1.5, U1.29, U1.39, U1.40
GP2: J2.4, U1.6
GP3: J2.3, U1.7
K1_D: D1.1, K1.2
K2_D: D2.1, K2.2
K3_D: D3.1, K3.2
K4_D: D4.1, K4.2
K5_D: D5.1, K5.2
K6_D: D6.1, K6.2
K7_D: D7.1, K7.2
K8_D: D8.1, K8.2
K9_D: D9.1, K9.2
K10_D: D10.1, K10.2
K11_D: D11.1, K11.2
K12_D: D12.1, K12.2
ROW0: D1.2, D2.2, D3.2, U1.23
ROW1: D4.2, D5.2, D6.2, U1.24
ROW2: D7.2, D8.2, D9.2, U1.25
ROW3: D10.2, D11.2, D12.2, U1.26

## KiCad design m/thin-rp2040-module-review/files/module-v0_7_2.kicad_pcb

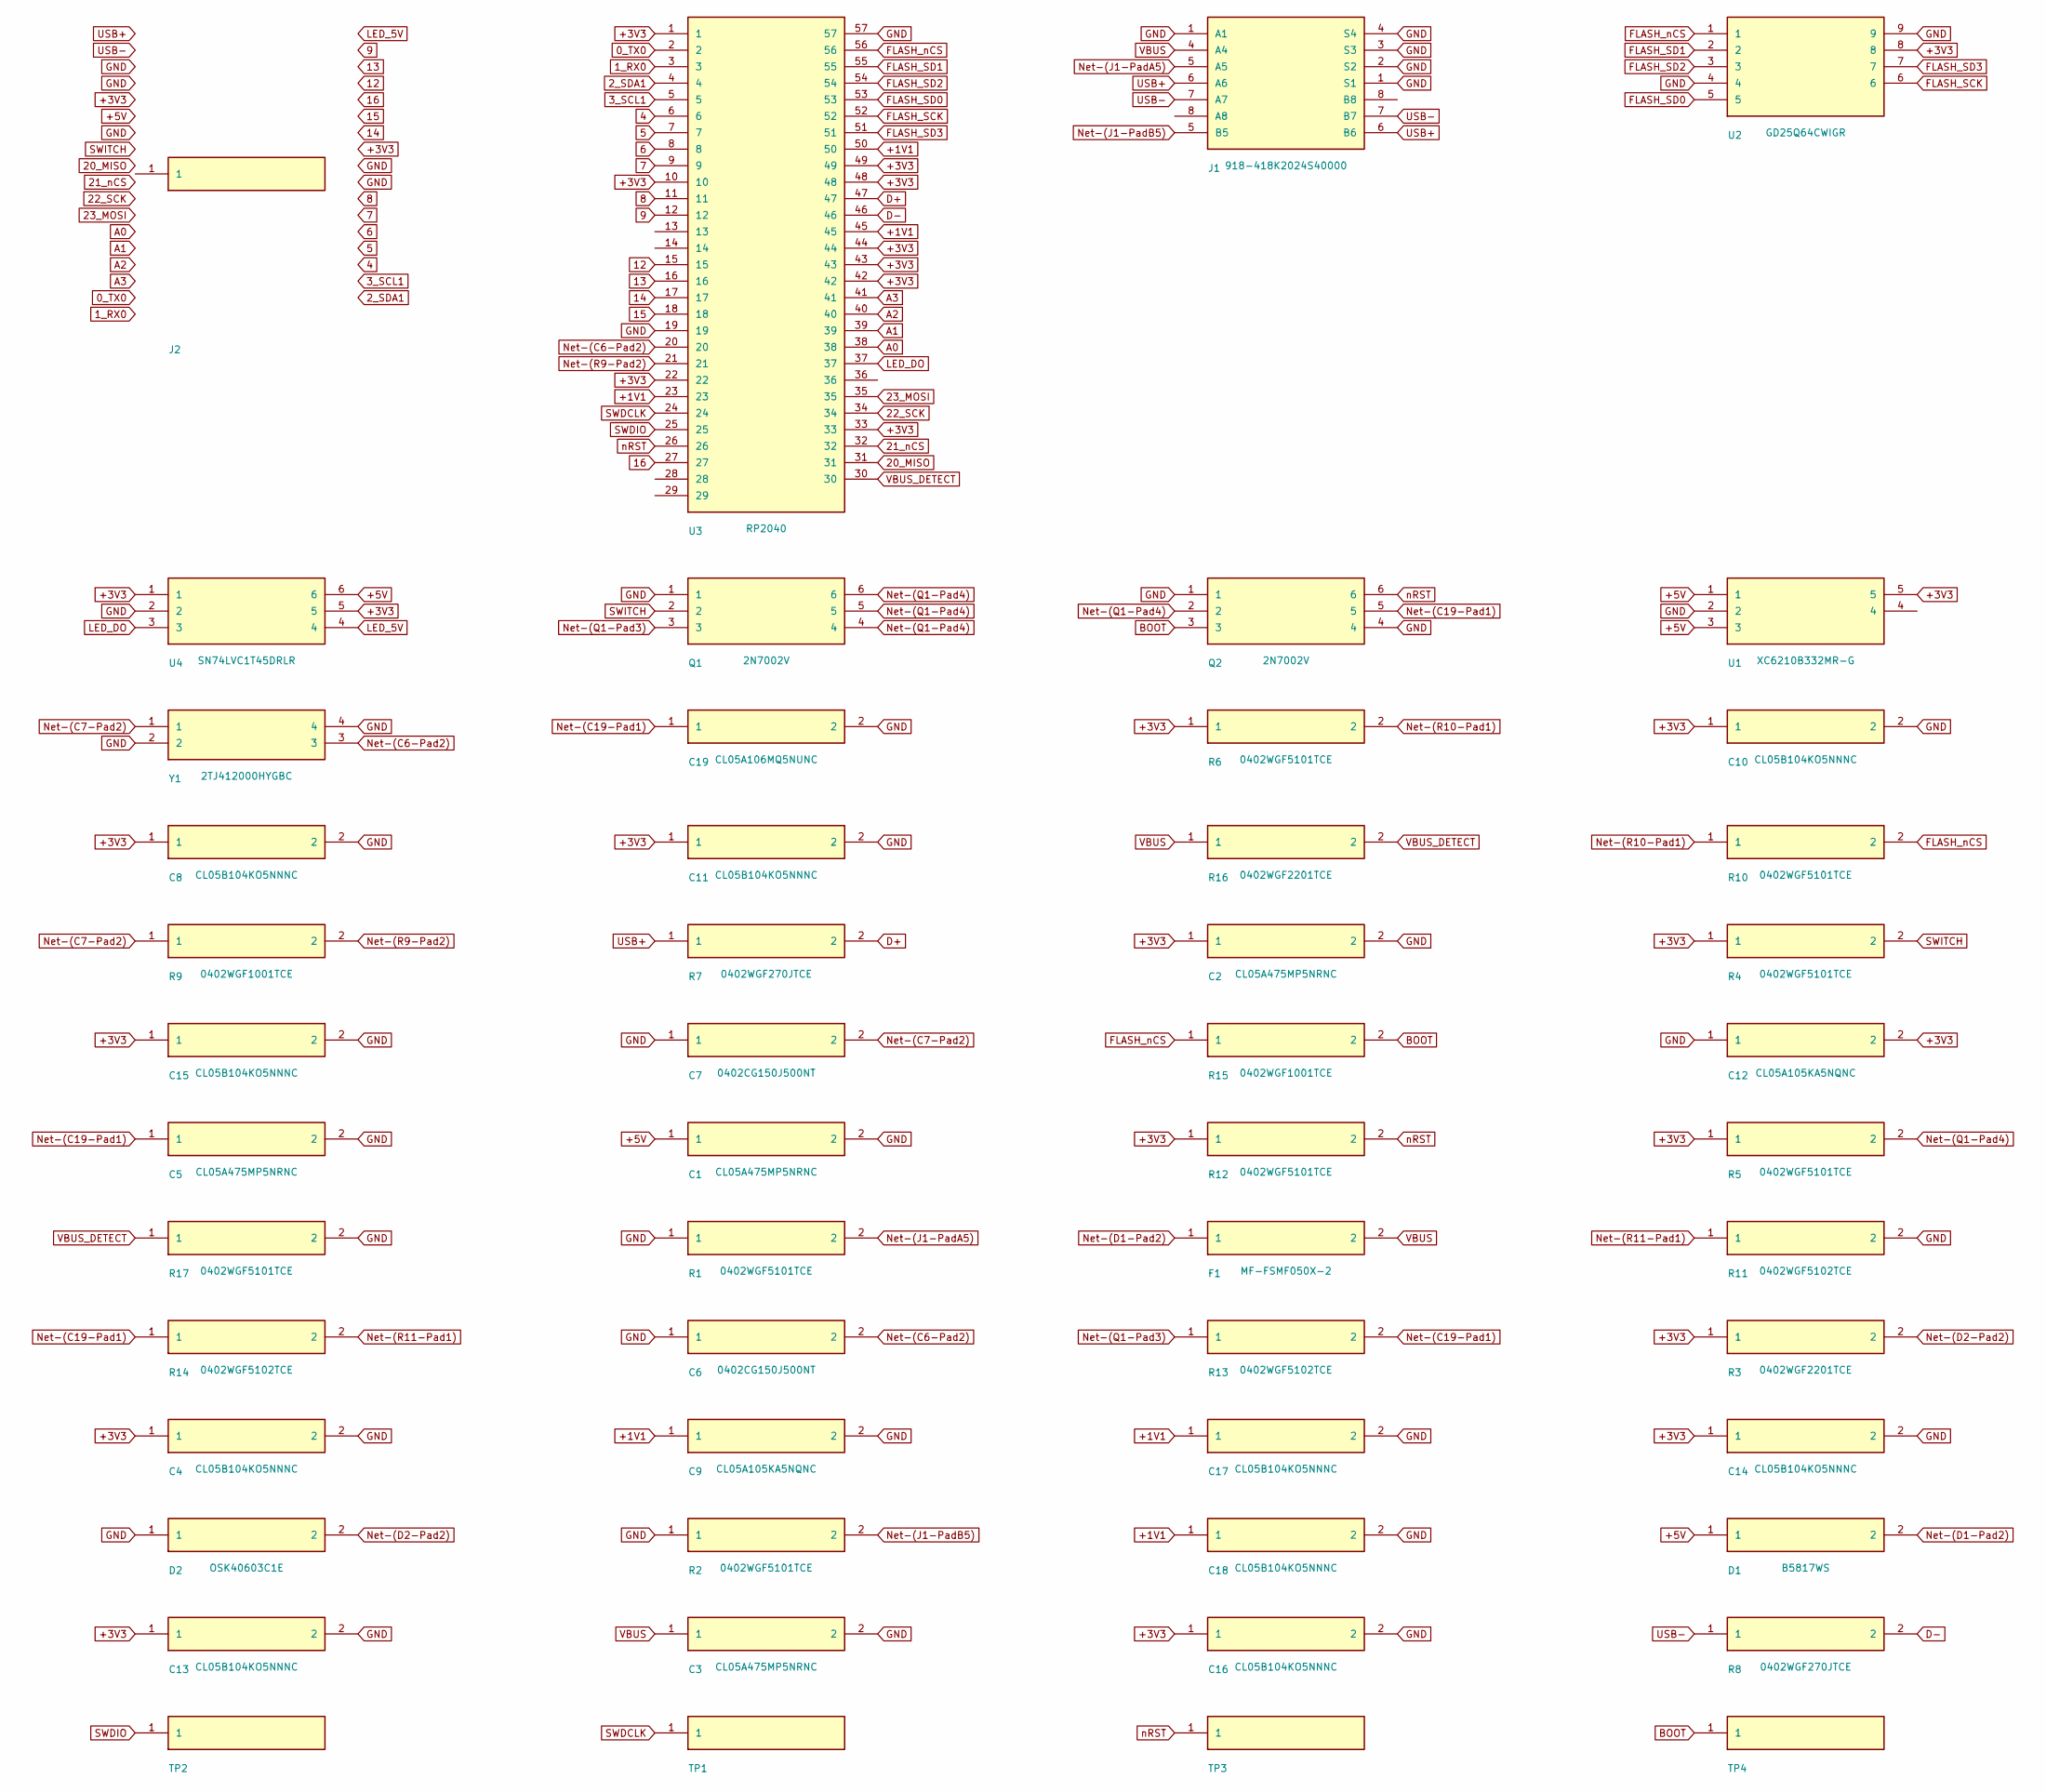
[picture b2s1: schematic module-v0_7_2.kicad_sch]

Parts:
C1, C2, C3, C5: CL05A475MP5NRNC
C4, C8, C10, C11, C13, C14, C15, C16, C17, C18: CL05B104KO5NNNC
C6, C7: 0402CG150J500NT
C9, C12: CL05A105KA5NQNC
C19: CL05A106MQ5NUNC
D1: B5817WS
D2: OSK40603C1E
F1: MF-FSMF050X-2
J1: 918-418K2024S40000
J2: (no value)
Q1, Q2: 2N7002V
R1, R2, R4, R5, R6, R10, R12, R17: 0402WGF5101TCE
R3, R16: 0402WGF2201TCE
R7, R8: 0402WGF270JTCE
R9, R15: 0402WGF1001TCE
R11, R13, R14: 0402WGF5102TCE
TP1, TP2, TP3, TP4: (no value)
U1: XC6210B332MR-G
U2: GD25Q64CWIGR
U3: RP2040
U4: SN74LVC1T45DRLR
Y1: 2TJ412000HYGBC

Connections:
+1V1: C9.1, C17.1, C18.1, U3.23, U3.45, U3.50
+3V3: C2.1, C4.1, C8.1, C10.1, C11.1, C12.2, C13.1, C14.1, C15.1, C16.1, J2.27, J2.35, R3.1, R4.1, R5.1, R6.1, R12.1, U1.5, U2.8, U3.1, U3.10, U3.22, U3.33, U3.42, U3.43, U3.44, U3.48, U3.49, U4.1, U4.5
+5V: C1.1, D1.1, J2.30, U1.1, U1.3, U4.6
/0_TX0: J2.2, U3.2
/1_RX0: J2.3, U3.3
/2_SDA1: J2.6, U3.4
/3_SCL1: J2.7, U3.5
/4: J2.8, U3.6
/5: J2.9, U3.7
/6: J2.10, U3.8
/7: J2.11, U3.9
/8: J2.12, U3.11
/9: J2.13, U3.12
/12: J2.14, U3.15
/13: J2.15, U3.16
/14: J2.16, U3.17
/15: J2.17, U3.18
/16: J2.18, U3.27
/20_MISO: J2.21, U3.31
/21_nCS: J2.19, U3.32
/22_SCK: J2.22, U3.34
/23_MOSI: J2.20, U3.35
/A0: J2.23, U3.38
/A1: J2.24, U3.39
/A2: J2.25, U3.40
/A3: J2.26, U3.41
/BOOT: Q2.3, R15.2, TP4.1
/D+: R7.2, U3.47
/D-: R8.2, U3.46
/FLASH_SCK: U2.6, U3.52
/FLASH_SD0: U2.5, U3.53
/FLASH_SD1: U2.2, U3.55
/FLASH_SD2: U2.3, U3.54
/FLASH_SD3: U2.7, U3.51
/FLASH_nCS: R10.2, R15.1, U2.1, U3.56
/LED_5V: J2.32, U4.4
/LED_DO: U3.37, U4.3
/SWDCLK: TP1.1, U3.24
/SWDIO: TP2.1, U3.25
/SWITCH: J2.28, Q1.2, R4.2
/USB+: J1.6 (A6), J2.1, R7.1
/USB-: J1.7 (A7), J2.31, R8.1
/VBUS_DETECT: R16.2, R17.1, U3.30
/nRST: Q2.6, R12.2, TP3.1, U3.26
unnamed: C6.2, U3.20, Y1.3
unnamed: C7.2, R9.1, Y1.1
unnamed: C5.1, C19.1, Q2.5, R13.2, R14.1
unnamed: D1.2, F1.1
unnamed: D2.2, R3.2
unnamed: Q1.3, R13.1
unnamed: Q1.4, Q1.5, Q1.6, Q2.2, R5.2
unnamed: R9.2, U3.21
unnamed: R6.2, R10.1
unnamed: R11.1, R14.2

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
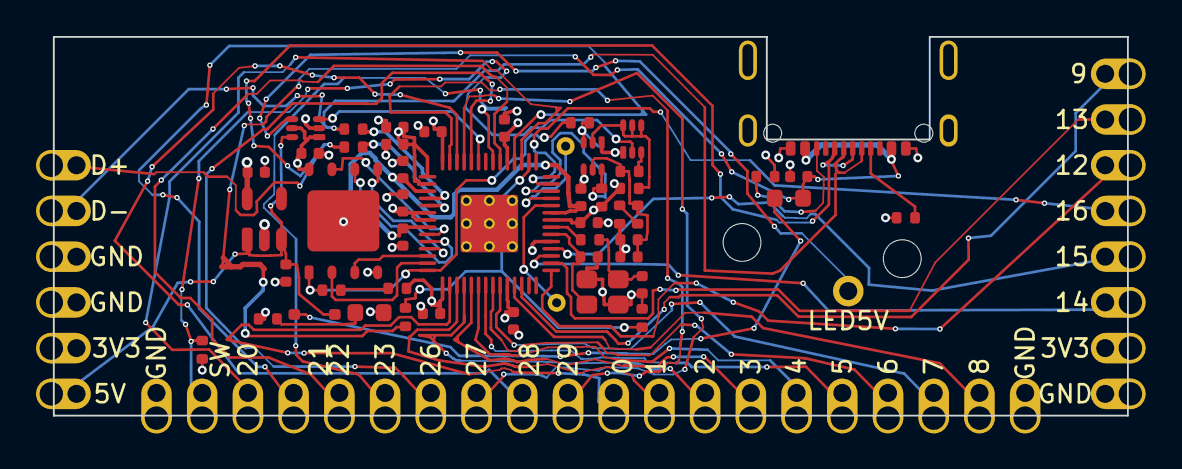
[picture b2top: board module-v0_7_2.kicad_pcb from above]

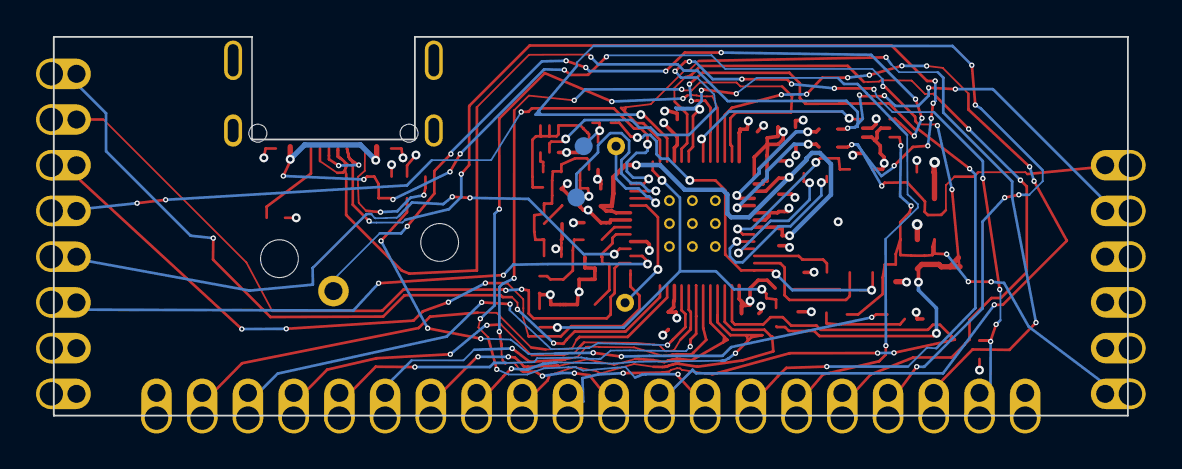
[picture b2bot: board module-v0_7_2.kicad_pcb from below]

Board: 4 copper layers, 59.7 x 21.0 mm, 52 parts (4 on the bottom side), 58 nets.
